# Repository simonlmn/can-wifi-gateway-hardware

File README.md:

# CAN/WiFi Gateway Hardware
Schematics and PCB layout for a CAN-WiFi gateway based on an ESP8266, an Arduino Nano and a CAN adapter/bridge.

Currently, there is only the DevBoard version available, which was designed to replace a prototype based on prototyping boards, some wires and a case. The dev board is meant to provide a more robust and reliable base for attaching and connecting the individual off-the-shelf components together:

 * An ESP8266 dev board ("NodeMCU Lolin V2")
 * An Arduino Nano V3
 * A CAN bus module based on MCP2515/TJA1050 with SPI (e.g. https://amzn.eu/d/gYvjiQy)
 * A power supply module (e.g. https://amzn.eu/d/45afEuz)

The shape and mounting hole pattern is designed to fit into an casing made for possibly moist/wet environments (https://sonoff.tech/product/accessories/ip66/), which is available from different vendors.

The (bare) PCBs can be directly ordered at https://aisler.net/simon-lehmann/can-wifi-gateway/can-wifi-gw-devboard. Of course, any other manufacturer can be used too.

This can be used for running https://github.com/simonlmn/can-wifi-gateway-stiebel-eltron to provide an HTTP-based API to a Stiebel Eltron heat pump.

<nobr></nobr>

## Support

If you want to support this project, you can:

 * use it and provide feedback
 * provide additional variations or versions (e.g. support for ESP32 or a fully integrated board)
 * 

## Functions

> [!NOTE]  
> The functionality behind each button/switch depends on the software running on the module. The picture below shows the intended functionality, which is also what the https://github.com/simonlmn/can-wifi-gateway-stiebel-eltron implements.

## Bill of Materials

Listed below are all components needed to fully assemble the DevBoard and mounting it in a fitting casing.

The listed prices are based on average prices from retailers (Germany), but sometimes only available when purchasing in "larger" quantities (e.g. a pack of five instead of just one). Most components can be interchanged for compatible variants from different manufacturers. The prices were last checked mid 2023.

### Electronic parts

| Part                                                                            | Quantity | Unit Price | Total Price |
| :------------------------------------------------------------------------------ | -------: | ---------: | ----------: |
| NodeMCU V2 (ESP8266/ESP-12F)                                                    |        1 |     5.00 € |      5.00 € |
| Arduino Nano V3 (ATmega328P)                                                    |        1 |     6.50 € |      6.50 € |
| MCP2515-based CAN Bus Shield                                                    |        1 |     6.50 € |      6.50 € |
| MP1584EN-based DC-DC Buck Converter 4.5-28V to 0.8-20V                          |        1 |     1.00 € |      1.00 € |
| 74LVC1T45GW Bus Transceiver, TSSOP-6                                            |        3 |     0.35 € |      1.05 € |
| PPTC-Fuse FSMD050-1210-R, 16 V, 500 mA                                          |        1 |     0.50 € |      0.50 € |
| 100 nF Capacitor, SMD 1206                                                      |        6 |     0.05 € |      0.30 € |
| 1 kOhm Resistor, SMD 0805                                                       |        1 |     0.05 € |      0.05 € |
| LED Yellow, SMD 0805                                                            |        1 |     0.10 € |      0.10 € |
| DIP-Switch, 4 Position, 2.54 mm, Through Hole                                   |        1 |     0.50 € |      0.50 € |
| Tactile Switch, 6 x 6 mm, 10 mm Stem Height, Through Hole                       |        3 |     0.10 € |      0.30 € |
| Sliding Switch, SPDT, 3-pin, Vertical, Through Hole                             |        1 |     0.20 € |      0.20 € |
| 2-pole Terminal Block, Screw Type, Horizontal, 5.08 mm, Through Hole            |        1 |     0.65 € |      0.65 € |
| 1x15-Pin Header, Female, 8.5 mm Socket Height, 2.54 mm, Through Hole            |        4 |     0.50 € |      2.00 € |
| 1x7-pin Header, Female, 8.5 mm Socket Height, 2.54 mm, Through Hole             |        1 |     0.30 € |      0.30 € |
| 1x2-Pin Header, Female, 8.5 mm Socket Height, 2.54 mm, Through Hole             |        5 |     0.15 € |      0.75 € |
| 1x2-Pin Header, Male, 8.5 mm Socket Height, 2.54 mm, Through Hole               |        5 |     0.05 € |      0.25 € |
| 2x3-Pin Header, Male, 8.5 mm Socket Height, 2.54 mm, Through Hole               |        1 |     0.25 € |      0.25 € |
| Jumper Shunt, 2.54 mm                                                           |        3 |     0.10 € |      0.30 € |
| __TOTAL__                                                                       |          |            | __26.50 €__ |

### Mechanical parts

| Part                                 | Quantity | Unit Price | Total Price |
| :----------------------------------- | -------: | ---------: | ----------: |
| Casing (dust/waterproof, IP66)       |        1 |     6.50 € |      6.50 € |
| Hex PCB Standoff M3, 10 mm + 6 mm  * |        6 |     0.15 € |      0.90 € |
| Screw M3, 8 mm                     * |        6 |     0.10 € |      0.60 € |
| Nut M3                             * |        2 |     0.10 € |      0.20 € |
| __TOTAL__                            |          |            |  __8.20 €__ |

 *) Standoffs, screws and nuts can be basically any material (i.e. nylon or metal). To screw them into the casing, the plastic mounting holes should be pre-tapped with an M3 tap in any case, but metal standoffs can be used as self-tapping.

## Notes on design choices

 * A separate Arduino Nano was used to interface with the CAN module to be able off-load some protocol handling from the ESP8266. While it could have been a better choice to upgrade to an ESP32 for more performance, this approach was a) what was available at the time and b) still seems to allow a more robust operation (the ESP8266 can be overloaded easily into unreliable operation).
 * Because the Arduino uses 5V and the ESP8266 3.3V the board makes use of specialized level shifting ICs. These may be over engineered, but they did  improve reliabililty compared to the prototype (where a resistor was used for level shifting).
 * The buttons and switches are placed and labeled for allowing inital set-up, configuration and testing/debugging in the field and are implemented as such by the CAN/WiFi gateway for Stiebel Eltron heatpumps. Except for the reset button, they can of course be used for other purposes or not used at all in other applications.

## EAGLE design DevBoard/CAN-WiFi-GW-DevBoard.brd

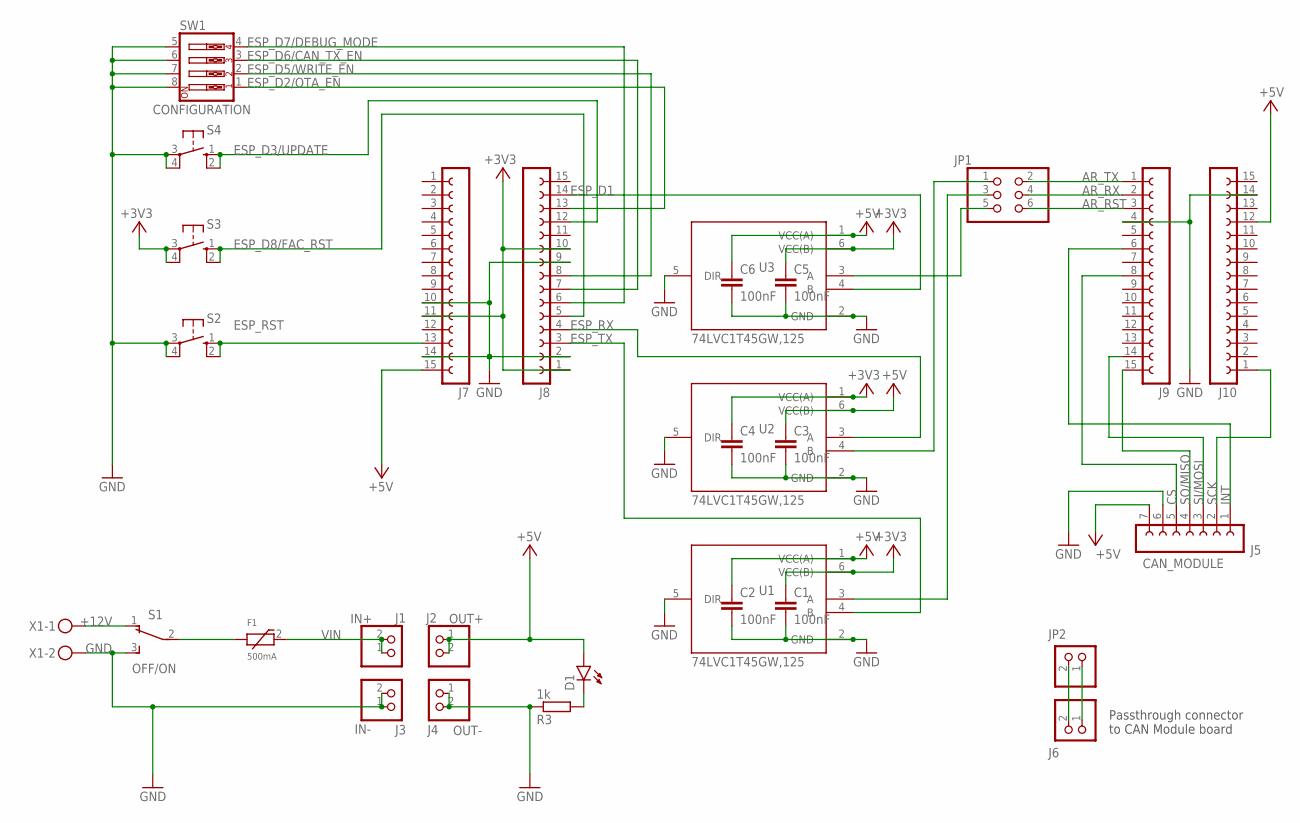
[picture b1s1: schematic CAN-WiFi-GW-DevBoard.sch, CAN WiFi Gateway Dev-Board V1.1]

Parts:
C1, C2, C3, C4, C5, C6: 100nF; C1206
D1: LEDSML0805; SML0805
F1: 500mA; FSMD050-1210-R
J1: IN+; 1X02
J2: OUT+; 1X02
J3: IN-; 1X02
J4: OUT-; 1X02
J5: CAN_MODULE; FE07
J6: PINHD-1X2; 1X02
J7, J8, J9, J10: FE15-1; FE15
JP1: PINHD-2X3; 2X03
JP2: PINHD-1X2; 1X02
R3: 1k; R0805
S1: OFF/ON; TL3XPO
S2, S3, S4: 10-XX; B3F-10XX
SW1: CONFIGURATION; EDG-04
U1, U2, U3: 74LVC1T45GW,125; SOP65P210X110-6N
X1: MKDSN1,5/2-5,08

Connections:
+3V3: C1.1, C4.1, C5.1, J7.11, J8.1, J8.10, S3.3, S3.4 (P1), U1.6 (VCC(B)), U2.1 (VCC(A)), U3.6 (VCC(B))
+5V: C2.1, C3.1, C6.1, D1.A, J2.1, J2.2, J5.7, J7.15, J10.12, U1.1 (VCC(A)), U2.6 (VCC(B)), U3.1 (VCC(A))
+12V: S1.1 (O), X1.1
AR_RST: J9.3, JP1.6
AR_RX: J9.2, JP1.4
AR_TX: J9.1, JP1.2
CS: J5.5, J9.8
ESP_D1: J8.14, U3.4 (B)
ESP_D2/OTA_EN: J8.13, SW1.1
ESP_D3/UPDATE: J8.12, S4.1 (S), S4.2 (S1)
ESP_D5/WRITE_EN: J8.8, SW1.2
ESP_D6/CAN_TX_EN: J8.7, SW1.3
ESP_D7/DEBUG_MODE: J8.6, SW1.4
ESP_D8/FAC_RST: J8.5, S3.1 (S), S3.2 (S1)
ESP_RST: J7.13, S2.1 (S), S2.2 (S1)
ESP_RX: J8.4, U2.3 (A)
ESP_RX_5V: JP1.1, U2.4 (B)
ESP_TX: J8.3, U1.4 (B)
ESP_TX_5V: JP1.3, U1.3 (A)
GND: C1.2, C2.2, C3.2, C4.2, C5.2, C6.2, J3.1, J3.2, J4.1, J4.2, J5.6, J7.10, J7.14, J8.2, J8.9, J9.4, J10.14, R3.1, S1.3 (S), S2.3, S2.4 (P1), S4.3, S4.4 (P1), SW1.5, SW1.6, SW1.7, SW1.8, U1.2 (GND), U1.5 (DIR), U2.2 (GND), U2.5 (DIR), U3.2 (GND), U3.5 (DIR), X1.2
INT: J5.1, J9.6
unnamed: D1.C, R3.2
unnamed: J6.1, JP2.1
unnamed: J6.2, JP2.2
unnamed: F1.1, S1.2
unnamed: JP1.5, U3.3 (A)
SCK: J5.2, J10.1
SI/MOSI: J5.3, J9.14
SO/MISO: J5.4, J9.15
VIN: F1.2, J1.1, J1.2

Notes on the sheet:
Passthrough connector to CAN Module board

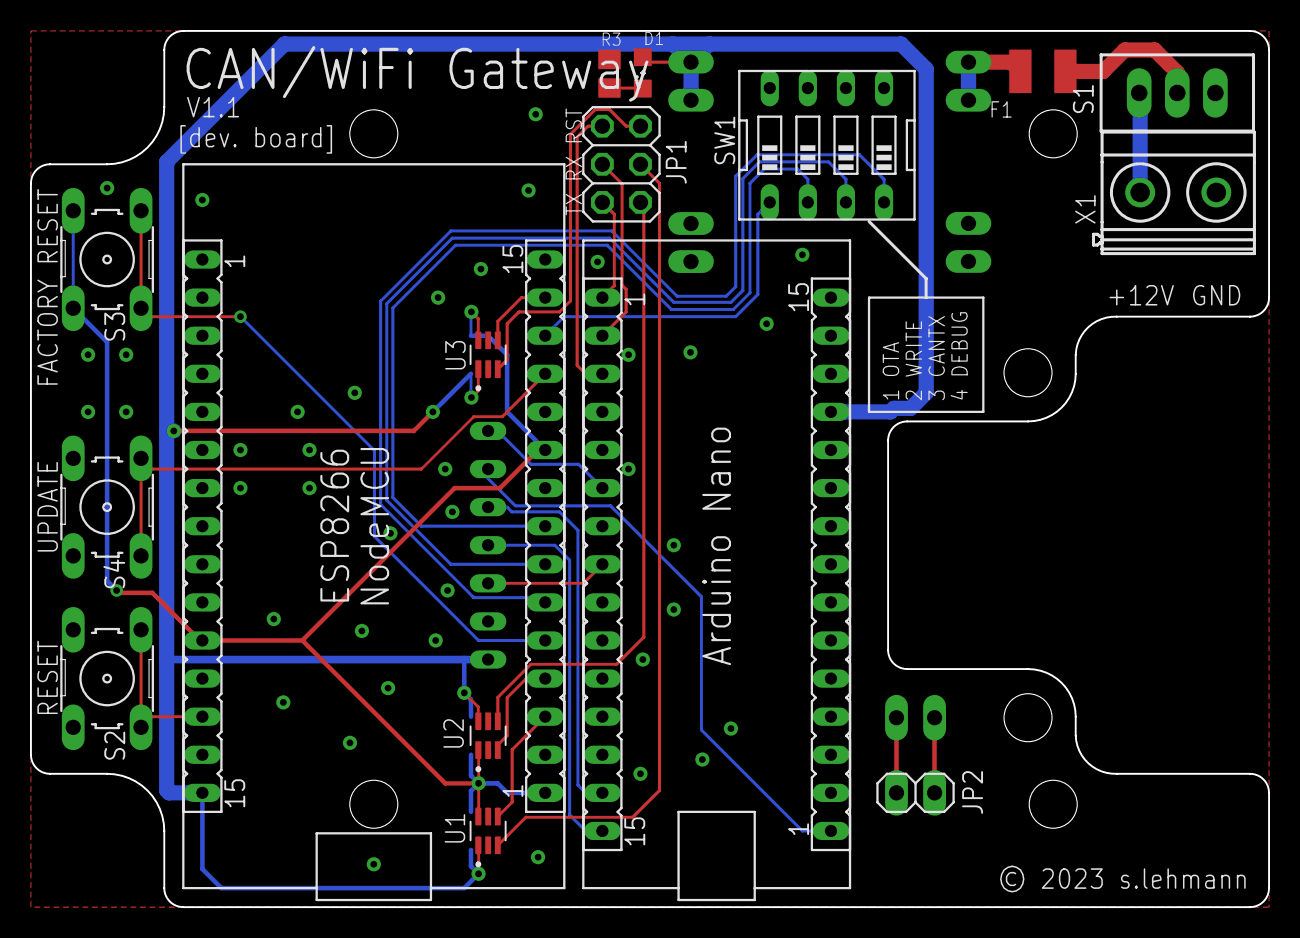
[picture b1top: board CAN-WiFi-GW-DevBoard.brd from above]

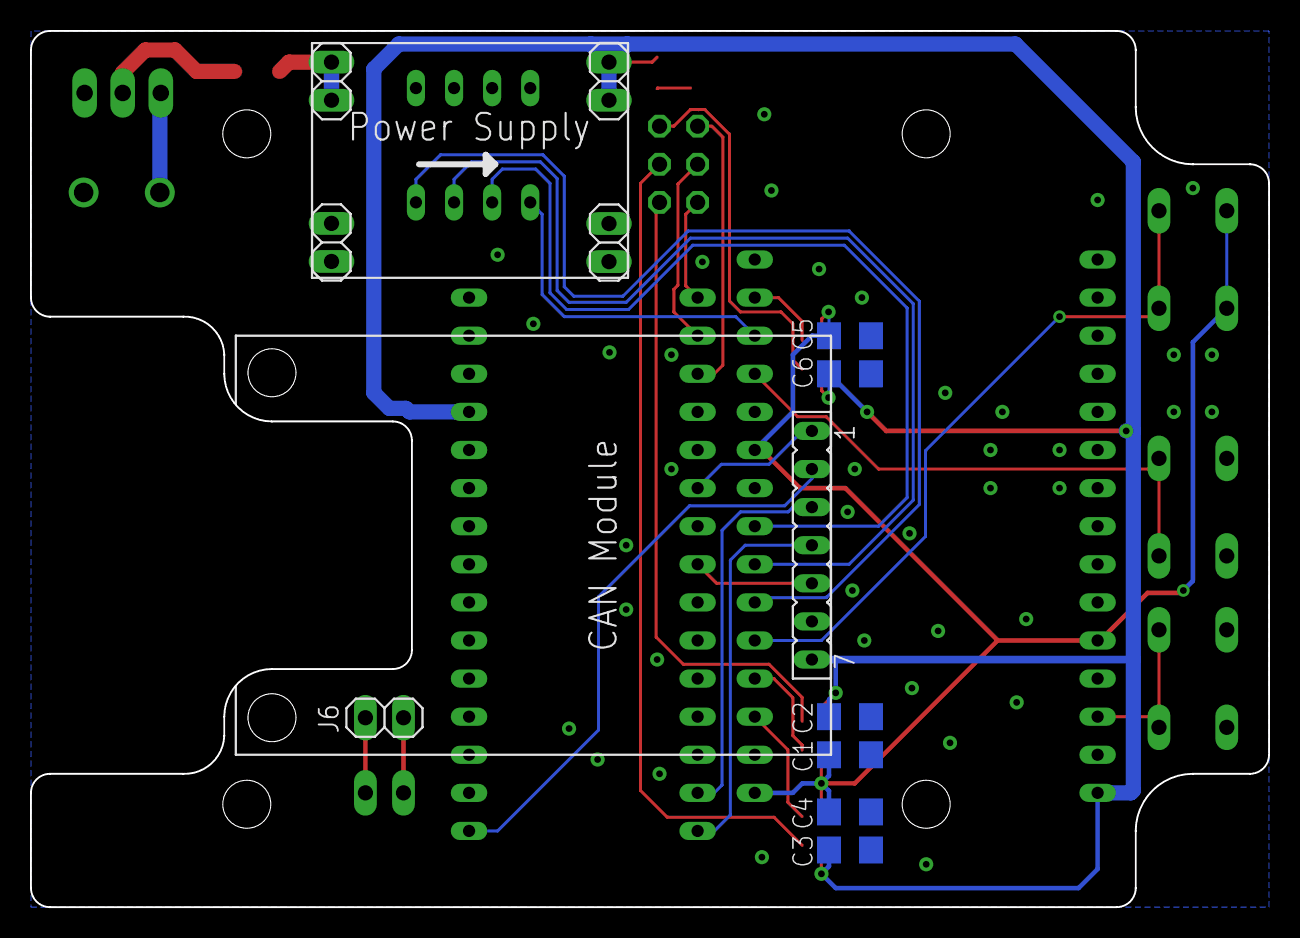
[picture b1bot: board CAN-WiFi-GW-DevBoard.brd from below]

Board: 2 copper layers, 82.5 x 58.4 mm, 30 parts (12 on the bottom side), 30 nets.

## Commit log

2023-04-25 First produced revision of dev-board.
2023-04-25 WIP attempt at creating an integrated board without pre-made dev-boards.
2023-04-25 Revision dev-board fixing button mistakes, physical dimensions and robustness.
2023-04-27 Fix labeling of config switches.
2023-04-27 Removed wire stub.
2023-08-16 Fix labelling of config switches
2023-08-16 Remove redundant diode before power supply
2023-08-20 Add BOM with approximate prices.
2023-08-24 Add pictures of DevBoard v1.0
2023-09-04 Add picture of unassembled board and components
2023-09-09 Add function overview
2023-09-11 Fix illustration of functions.
2023-09-11 Add power terminal and switch

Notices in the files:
DevBoard/CAN-WiFi-GW-DevBoard.brd:
© 2023 s.lehmann
